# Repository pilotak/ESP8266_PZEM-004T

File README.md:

# ESP_PZEM
## UNDER TESTING, FW under development
Board based on ESP8266-01 provides serial between with single or multiple PZEM-004T (with multiplexing). Built-in auto reset feature when uploading (GPIO0 is LOW). Fits above/under PZEM-004T board.

## BOM
### Single PZEM
Solder both jumpers to B

Qty | Value |Package
---|:---|:---
2 | 100n | 0805
1 | 100uF/6.3V | SMC_B
2 | BAT54C | SOT-23
1 | ESP01S | ESP-01
1 | FTDI_CONN | PINHEAD-6 
2 | BSS138 | SOT23
8 | 10K | 0805
1 | AC-DC-3.5W | AC-DC-3.5W
1 | LM1117-3.3 | SOT223
2 | KF301-5.0-2P | KF301-5.0-2P
1 | S4B-XH-A-1 | JST-XH-04-RIGHT-ANGLE

### Up to 4 PZEMs
Solder both jumpers to A

add to above

Qty | Value |Package
---|:---|:---
1 | 100n | 0805
1 | 74HC4052D | SO16
1 | 10K | 0805
3 | S4B-XH-A-1 | JST-XH-04-RIGHT-ANGLE

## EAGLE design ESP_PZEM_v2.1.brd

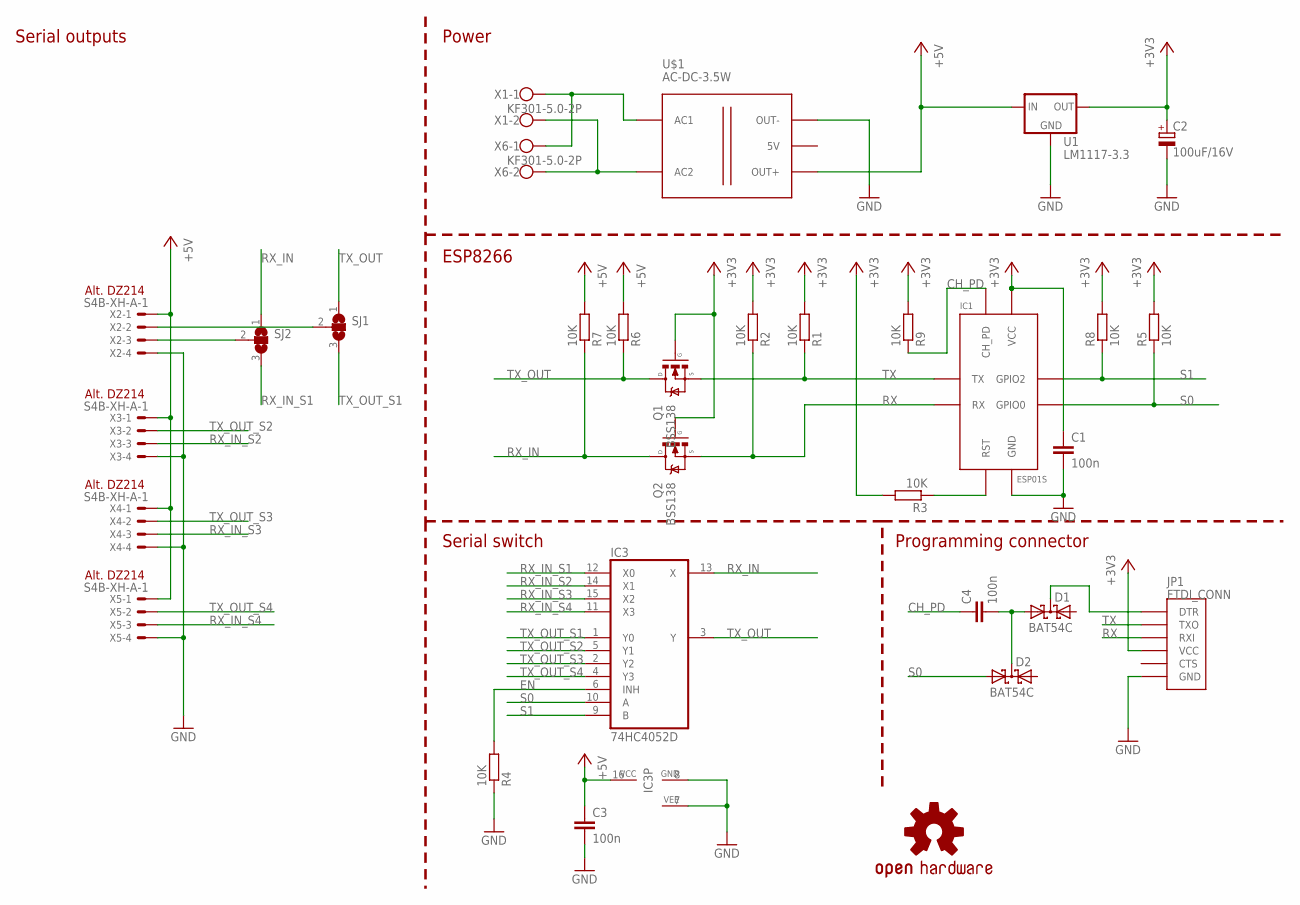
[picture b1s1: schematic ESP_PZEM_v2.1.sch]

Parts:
C1, C3, C4: 100n; C0805
C2: 100uF/16V; SMC_B
D1, D2: BAT54C; SOT23
IC1: ESP01S; ESP-01
IC3: 74HC4052D; SO16
JP1: FTDI_CONN; FTDI
LOGO1: OSHW-LOGOL; OSHW-LOGO-L
Q1, Q2: BSS138; SOT23
R1, R2, R3, R4, R5, R6, R7, R8, R9: 10K; R0805
SJ1, SJ2: SJ2W; SJ_2
U1: LM1117-3.3; SOT223
U$1: AC-DC-3.5W
X1, X6: KF301-5.0-2P
X2, X3, X4, X5: S4B-XH-A-1; JST-XH-04-PACKAGE-RIGHT

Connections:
+3V3: C1.1, C2.+, IC1.VCC, JP1.P$4 (VCC), Q1.1 (G), Q2.1 (G), R1.2, R2.2, R3.2, R5.2, R8.2, R9.2, U1.2 (OUT), U1.4 (OUT)
+5V: C3.1, IC3.16 (VCC), R6.2, R7.2, U1.3 (IN), U$1.J2.3 (OUT+), X2.1, X3.1, X4.1, X5.1
CH_PD: C4.1, IC1.CH_PD, R9.1
EN: IC3.6 (INH), R4.2
GND: C1.2, C2.-, C3.2, IC1.GND, IC3.7 (VEE), IC3.8 (GND), JP1.P$6 (GND), R4.1, U1.1 (GND), U$1.J2.1 (OUT-), X2.4, X3.4, X4.4, X5.4
L: U$1.J1.1 (AC1), X1.1, X6.1
N: U$1.J1.2 (AC2), X1.2, X6.2
unnamed: IC1.RST, R3.1
unnamed: C4.2, D1.1 (A1), D2.3 (CC)
unnamed: SJ1.2, X2.2
unnamed: SJ2.2, X2.3
unnamed: D1.3 (CC), JP1.P$1 (DTR)
RX: IC1.RX, JP1.P$3 (RXI), Q2.2 (S), R2.1
RX_IN: IC3.13 (X), Q2.3 (D), R7.1, SJ2.1
RX_IN_S1: IC3.12 (X0), SJ2.3
RX_IN_S2: IC3.14 (X1), X3.3
RX_IN_S3: IC3.15 (X2), X4.3
RX_IN_S4: IC3.11 (X3), X5.3
S0: D2.1 (A1), IC1.GPIO0, IC3.10 (A), R5.1
S1: IC1.GPIO2, IC3.9 (B), R8.1
TX: IC1.TX, JP1.P$2 (TXO), Q1.2 (S), R1.1
TX_OUT: IC3.3 (Y), Q1.3 (D), R6.1, SJ1.1
TX_OUT_S1: IC3.1 (Y0), SJ1.3
TX_OUT_S2: IC3.5 (Y1), X3.2
TX_OUT_S3: IC3.2 (Y2), X4.2
TX_OUT_S4: IC3.4 (Y3), X5.2

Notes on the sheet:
ESP8266
Power
Serial outputs
Serial switch
Programming connector
Alt. DZ214

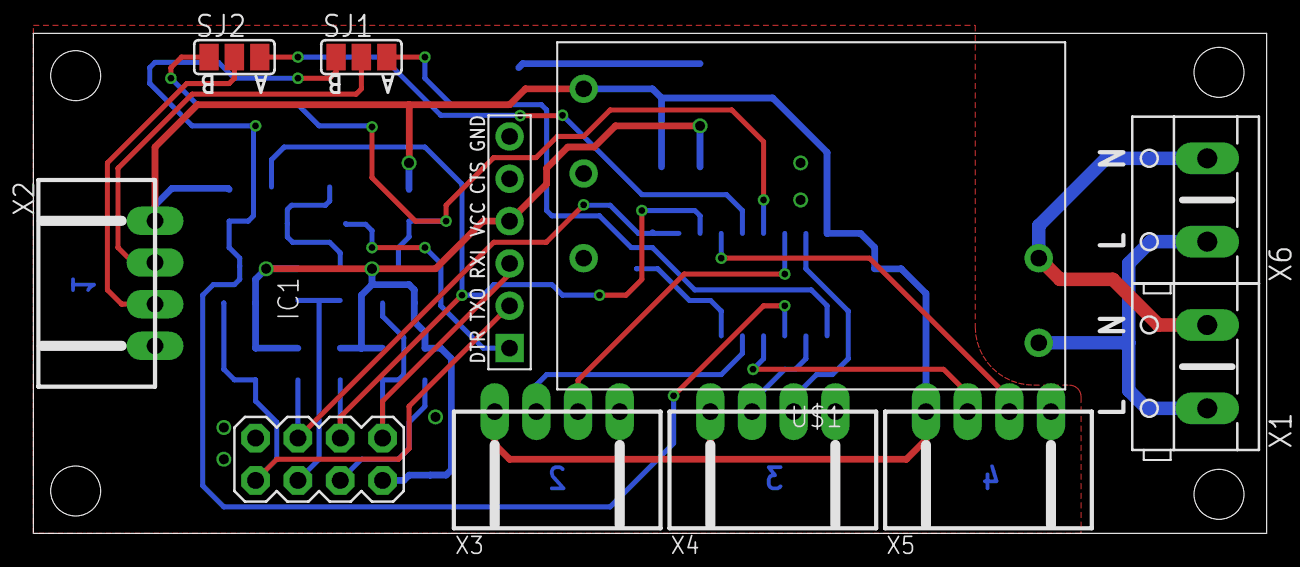
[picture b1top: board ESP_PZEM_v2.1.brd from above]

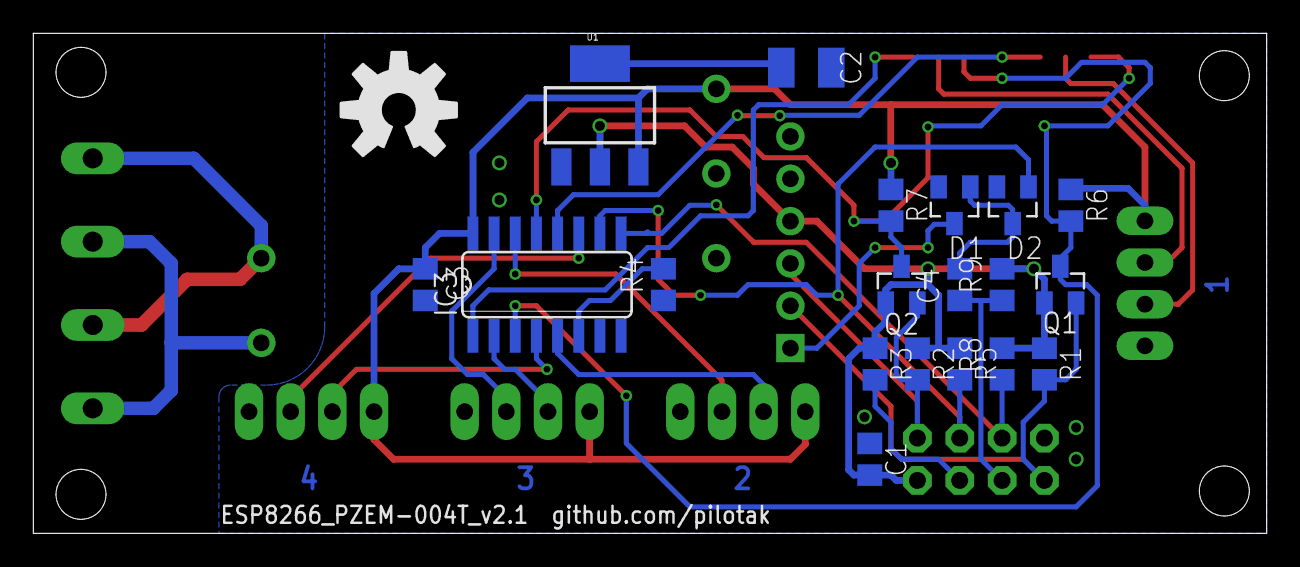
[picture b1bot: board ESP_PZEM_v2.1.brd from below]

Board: 2 copper layers, 74.0 x 30.0 mm, 31 parts (20 on the bottom side), 26 nets.

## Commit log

2018-01-14 init
2018-01-14 SS16 -> BAT54C
2018-01-15 resistor moved
2018-03-07 licence change

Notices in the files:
parts and their libraries:
diy-modules: Released under the Creative Commons Attribution 4.0 International License: http://creativecommons.org/licenses/by/4.0
SparkFun-Aesthetics: Licensing: Creative Commons ShareAlike 4.0 International - https://creativecommons.org/licenses/by-sa/4.0
